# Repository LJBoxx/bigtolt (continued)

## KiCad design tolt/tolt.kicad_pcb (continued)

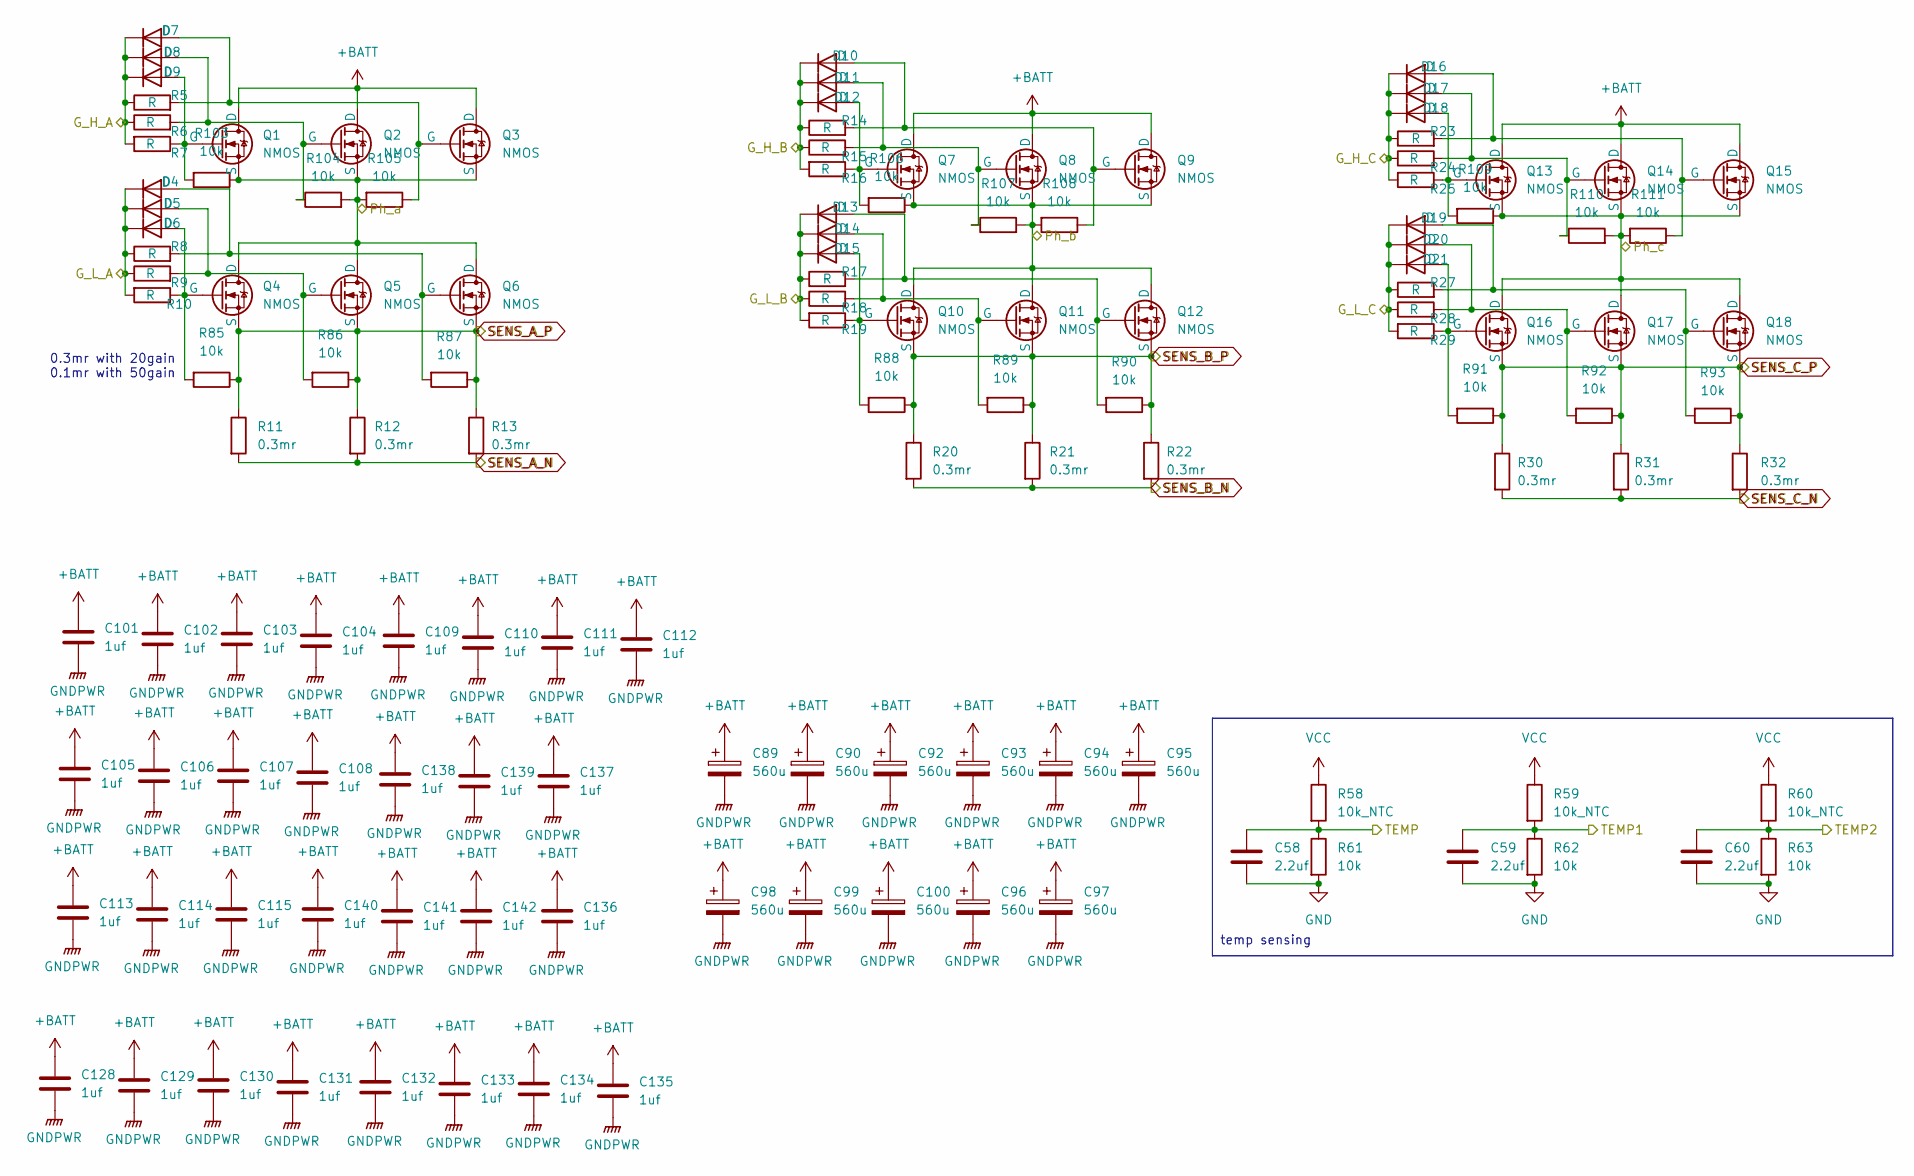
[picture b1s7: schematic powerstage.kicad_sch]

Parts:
C58, C59, C60: 2.2uf; C_0603_1608Metric
C89, C90, C92, C93, C94, C95, C96, C97, C98, C99, C100: 560u; CP_Radial_D16.0mm_P7.50mm
C101, C102, C103, C104, C105, C106, C107, C108, C109, C110, C111, C112, C113, C114, C115, C128, C129, C130, C131, C132, C133, C134, C135, C136, C137, C138, C139, C140, C141, C142: 1uf; C_2220_5750Metric_Pad1.97x5.40mm_HandSolder
D4, D5, D6, D7, D8, D9, D10, D11, D12, D13, D14, D15, D16, D17, D18, D19, D20, D21: D; D_SOD-123
Q1, Q2, Q3, Q4, Q5, Q6, Q7, Q8, Q9, Q10, Q11, Q12, Q13, Q14, Q15, Q16, Q17, Q18: NMOS; HDSOP-16-2
R5, R6, R7, R8, R9, R10, R14, R15, R16, R17, R18, R19, R23, R24, R25, R27, R28, R29: R; R_0805_2012Metric
R11, R12, R13, R20, R21, R22, R30, R31, R32: 0.3mr; R5930
R58, R59, R60: 10k_NTC; R_0603_1608Metric_Pad0.98x0.95mm_HandSolder
R61, R62, R63, R85, R86, R87, R88, R89, R90, R91, R92, R93, R103, R104, R105, R106, R107, R108, R109, R110, R111: 10k; R_0603_1608Metric

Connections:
+BATT: C89.1, C90.1, C92.1, C93.1, C94.1, C95.1, C96.1, C97.1, C98.1, C99.1, C100.1, C101.1, C102.1, C103.1, C104.1, C105.1, C106.1, C107.1, C108.1, C109.1, C110.1, C111.1, C112.1, C113.1, C114.1, C115.1, C128.1, C129.1, C130.1, C131.1, C132.1, C133.1, C134.1, C135.1, C136.1, C137.1, C138.1, C139.1, C140.1, C141.1, C142.1, Q1.1 (D), Q2.1 (D), Q3.1 (D), Q7.1 (D), Q8.1 (D), Q9.1 (D), Q13.1 (D), Q14.1 (D), Q15.1 (D); also elsewhere on the board
/INTER/G_H_A: D7.1 (K), D8.1 (K), D9.1 (K), R5.1, R6.1, R7.2; also elsewhere on the board
/INTER/G_H_B: D10.1 (K), D11.1 (K), D12.1 (K), R14.1, R15.1, R16.2; also elsewhere on the board
/INTER/G_H_C: D16.1 (K), D17.1 (K), D18.1 (K), R23.1, R24.1, R25.2; also elsewhere on the board
/INTER/G_L_A: D4.1 (K), D5.1 (K), D6.1 (K), R8.1, R9.1, R10.2; also elsewhere on the board
/INTER/G_L_B: D13.1 (K), D14.1 (K), D15.1 (K), R17.1, R18.1, R19.2; also elsewhere on the board
/INTER/G_L_C: D19.1 (K), D20.1 (K), D21.1 (K), R27.1, R28.1, R29.2; also elsewhere on the board
/INTER/Ph_a: Q1.3 (S), Q2.3 (S), Q3.3 (S), Q4.1 (D), Q5.1 (D), Q6.1 (D), R103.1, R104.2, R105.2; also elsewhere on the board
/INTER/Ph_b: Q7.3 (S), Q8.3 (S), Q9.3 (S), Q10.1 (D), Q11.1 (D), Q12.1 (D), R106.1, R107.2, R108.2; also elsewhere on the board
/INTER/Ph_c: Q13.3 (S), Q14.3 (S), Q15.3 (S), Q16.1 (D), Q17.1 (D), Q18.1 (D), R109.1, R110.2, R111.2; also elsewhere on the board
/logic/ADC_T1: C58.1, R58.2, R61.1; also elsewhere on the board
/logic/ADC_T2: C59.1, R59.2, R62.1; also elsewhere on the board
/logic/ADC_T3: C60.1, R60.2, R63.1; also elsewhere on the board
GND: C58.2, C59.2, C60.2, R61.2, R62.2, R63.2; also elsewhere on the board
GNDPWR: C89.2, C90.2, C92.2, C93.2, C94.2, C95.2, C96.2, C97.2, C98.2, C99.2, C100.2, C101.2, C102.2, C103.2, C104.2, C105.2, C106.2, C107.2, C108.2, C109.2, C110.2, C111.2, C112.2, C113.2, C114.2, C115.2, C128.2, C129.2, C130.2, C131.2, C132.2, C133.2, C134.2, C135.2, C136.2, C137.2, C138.2, C139.2, C140.2, C141.2, C142.2; also elsewhere on the board
unnamed: D4.2 (A), Q6.2 (G), R8.2, R87.2
unnamed: D5.2 (A), Q5.2 (G), R9.2, R86.2
unnamed: D6.2 (A), Q4.2 (G), R10.1, R85.2
unnamed: D7.2 (A), Q3.2 (G), R5.2, R105.1
unnamed: D8.2 (A), Q2.2 (G), R6.2, R104.1
unnamed: D9.2 (A), Q1.2 (G), R7.1, R103.2
unnamed: D10.2 (A), Q9.2 (G), R14.2, R108.1
unnamed: D11.2 (A), Q8.2 (G), R15.2, R107.1
unnamed: D12.2 (A), Q7.2 (G), R16.1, R106.2
unnamed: D13.2 (A), Q12.2 (G), R17.2, R90.2
unnamed: D14.2 (A), Q11.2 (G), R18.2, R89.2
unnamed: D15.2 (A), Q10.2 (G), R19.1, R88.2
unnamed: D16.2 (A), Q15.2 (G), R23.2, R111.1
unnamed: D17.2 (A), Q14.2 (G), R24.2, R110.1
unnamed: D18.2 (A), Q13.2 (G), R25.1, R109.2
unnamed: D19.2 (A), Q18.2 (G), R27.2, R93.2
unnamed: D20.2 (A), Q17.2 (G), R28.2, R92.2
unnamed: D21.2 (A), Q16.2 (G), R29.1, R91.2
SENS_A_N: R11.2, R12.2, R13.2; also elsewhere on the board
SENS_A_P: Q4.3 (S), Q5.3 (S), Q6.3 (S), R11.1, R12.1, R13.1, R85.1, R86.1, R87.1; also elsewhere on the board
SENS_B_N: R20.2, R21.2, R22.2; also elsewhere on the board
SENS_B_P: Q10.3 (S), Q11.3 (S), Q12.3 (S), R20.1, R21.1, R22.1, R88.1, R89.1, R90.1; also elsewhere on the board
SENS_C_N: R30.2, R31.2, R32.2; also elsewhere on the board
SENS_C_P: Q16.3 (S), Q17.3 (S), Q18.3 (S), R30.1, R31.1, R32.1, R91.1, R92.1, R93.1; also elsewhere on the board
VCC: R58.1, R59.1, R60.1; also elsewhere on the board

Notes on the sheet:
0.3mr with 20gain 0.1mr with 50gain
temp sensing

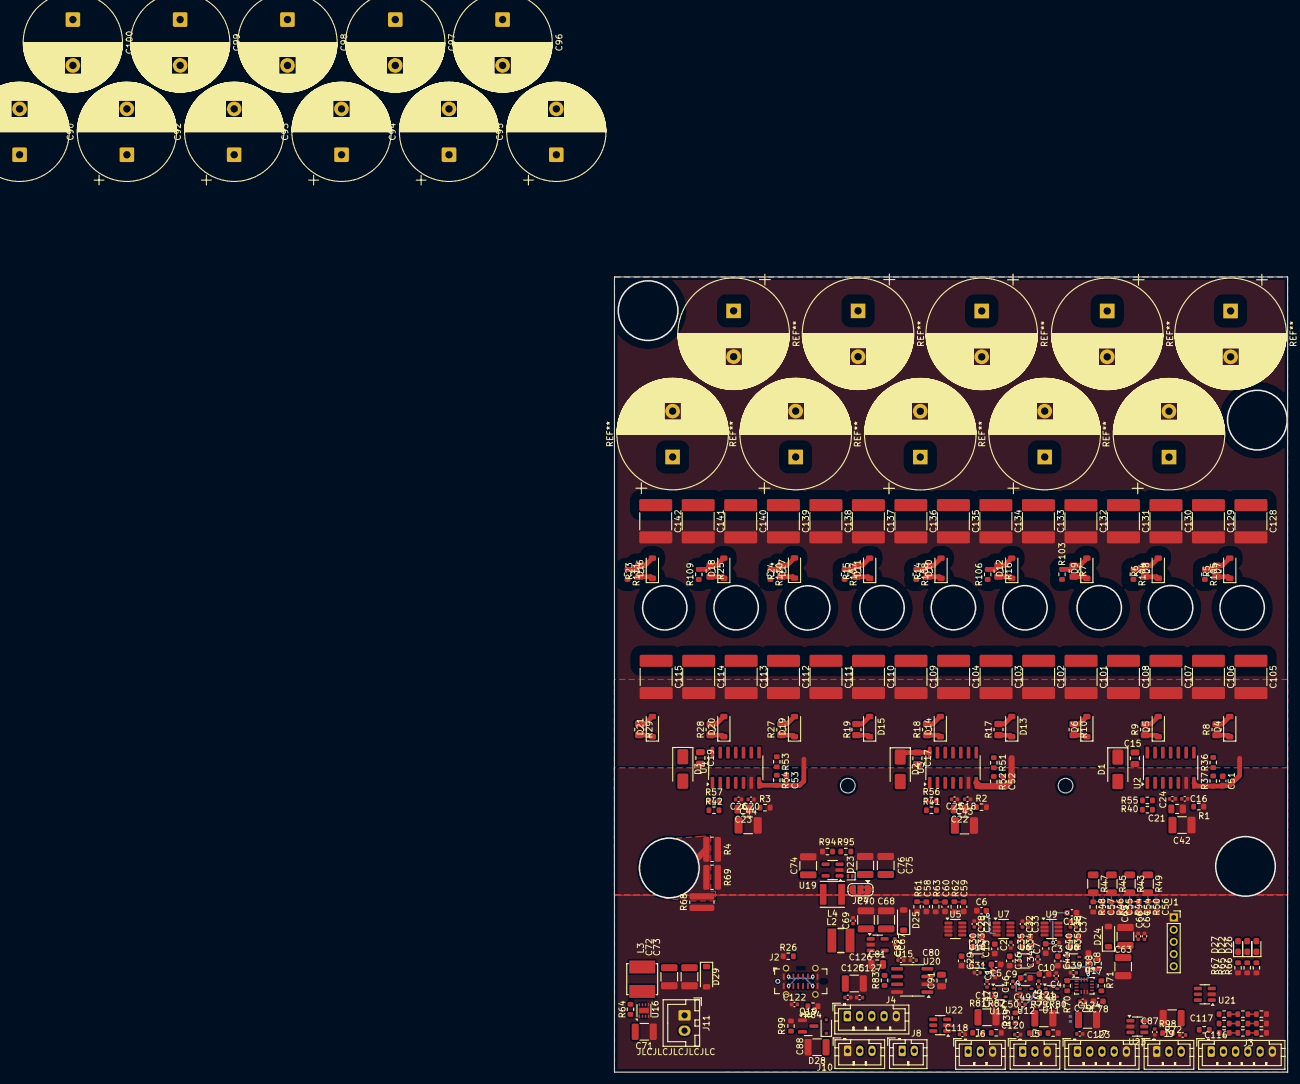
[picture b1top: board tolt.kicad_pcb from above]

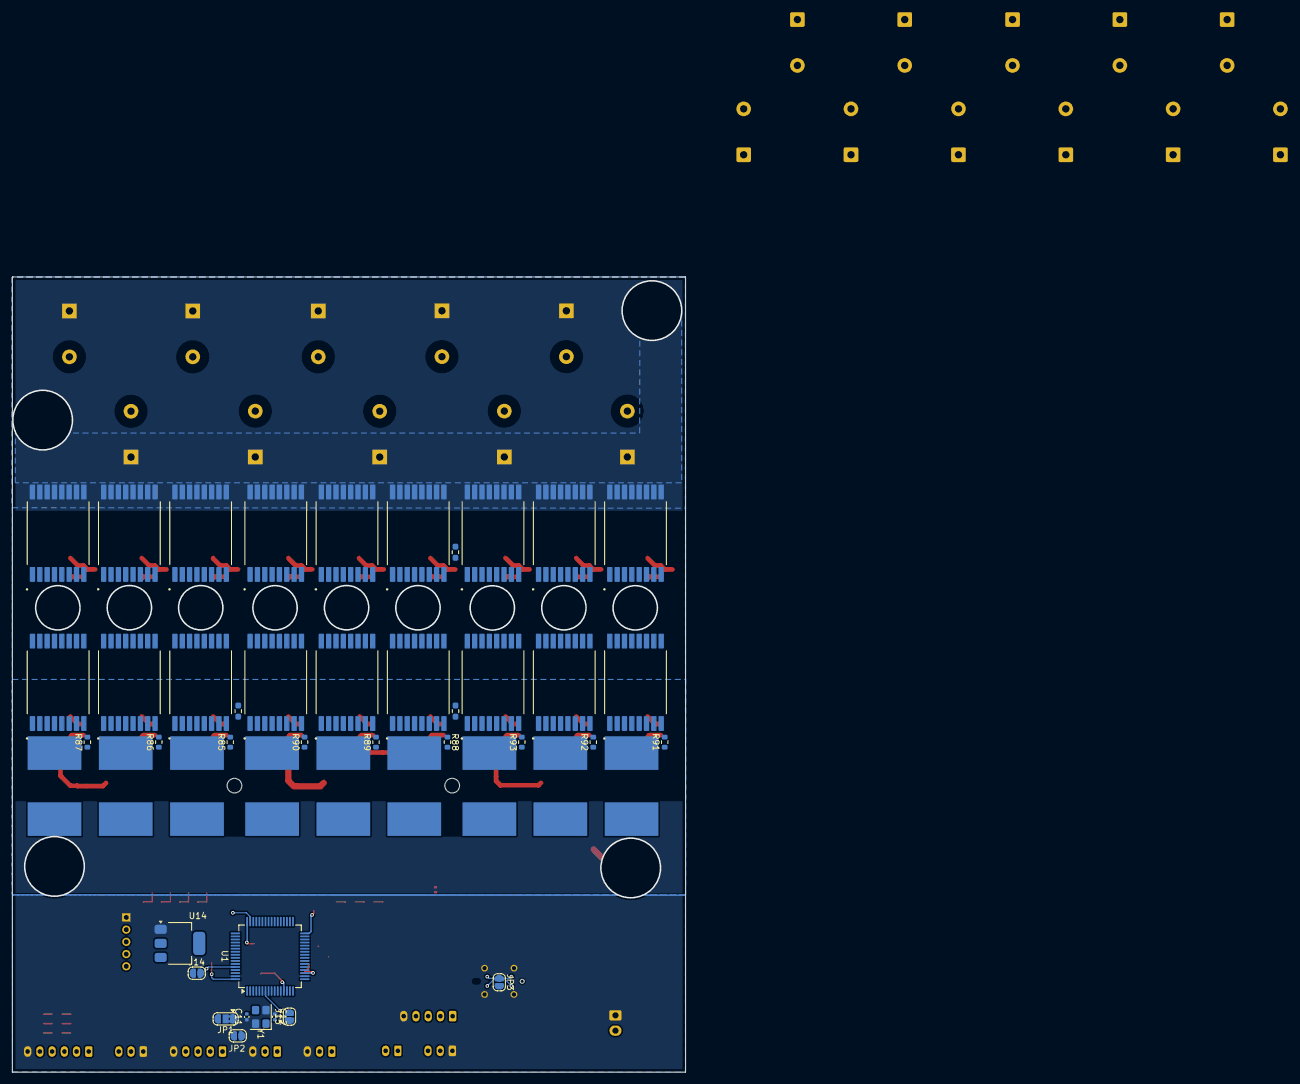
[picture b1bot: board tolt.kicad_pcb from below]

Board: 6 copper layers, 110.1 x 130.0 mm, 335 parts (49 on the bottom side), 130 nets.

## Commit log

2025-07-04 new file: tolt/desktop.ini new file: tolt/stm32.kicad_sch new file: tolt/tolt.kicad_pcb new file: tolt/tolt.kicad_pro new file: tolt/tolt.kicad_sch
2025-07-04 deleted: tolt/desktop.ini
2025-07-04 new file: tolt/inter.kicad_sch modified: tolt/tolt.kicad_pro modified: tolt/tolt.kicad_sch
2025-07-05 link
2025-07-05 new file: tolt/sheet.kicad_wks modified: tolt/sheet.kicad_wks modified: tolt/tolt.kicad_pro modified: tolt/tolt.kicad_sch
2025-07-05 modified: tolt/sheet.kicad_wks modified: tolt/tolt.kicad_pro modified: tolt/tolt.kicad_sch
2025-07-05 modified: tolt/inter.kicad_sch modified: tolt/stm32.kicad_sch
2025-07-05 new file: tolt/powerstage.kicad_sch modified: tolt/stm32.kicad_sch modified: tolt/tolt.kicad_pro modified: tolt/tolt.kicad_sch
2025-07-05 modified: tolt/inter.kicad_sch modified: tolt/powerstage.kicad_sch
2025-07-06 i hate RC Filters
2025-07-06 modified: tolt/inter.kicad_sch modified: tolt/stm32.kicad_sch modified: tolt/tolt.kicad_sch
2025-07-06 modified: tolt/inter.kicad_sch modified: tolt/powerstage.kicad_sch modified: tolt/stm32.kicad_sch modified: tolt/tolt.kicad_sch
2025-07-07 Converters
2025-07-07 new file: ESP32-C3_SUPERMINI_SMD.step new file: tolt/Library.pretty/MODULE_ESP32-C3_SUPERMINI.kicad_mod new file: tolt/auxl.kicad_sch
2025-07-08 modified: tolt/converters.kicad_sch modified: tolt/inter.kicad_sch modified: tolt/stm32.kicad_sch modified: tolt/tolt.kicad_pcb modified: tolt/tolt.kicad_pro modified: tolt/tolt.kicad_sch
2025-07-08 modified: tolt/auxl.kicad_sch modified: tolt/converters.kicad_sch modified: tolt/powerstage.kicad_sch modified: tolt/stm32.kicad_sch modified: tolt/tolt.kicad_pcb modified: tolt/tolt.kicad_pro modifi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
2025-07-08 new file: SOP120P1500X235-17N.step new file: tolt/Library.pretty/HDSOP-16-2.kicad_mod new file: tolt/Library.pretty/R5930.kicad_mod new file: tolt/conn.kicad_sch
2025-07-09 Revert "Merge branch 'main' of https://github.com/LJBoxx/bigtolt"
    This reverts commit 648dc93627ac55c8b54fa74faadbb35a312ea564, reversing
    changes made to 972c1c2491e13322900779e00755fdd65e6f8c8a.
2025-07-09 Reapply "Merge branch 'main' of https://github.com/LJBoxx/bigtolt"
    This reverts commit 10d1035653869a11abcc4dc45a35a471baa73785.
2025-07-09 revert the mess
    i am stupid
2025-07-09 6 layer
2025-07-10 footprints
2025-07-11 new file: tolt/Library.pretty/IND-SMD_L3.9-W3.9-1.kicad_mod new file: tolt/Library.pretty/IND-SMD_L5.0-W5.0.kicad_mod modified: tolt/auxl.kicad_sch modified: tolt/conn.kicad_sch modified: tolt/conver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
2025-07-11 modified: tolt/converters.kicad_sch modified: tolt/inter.kicad_sch modified: tolt/tolt.kicad_sch
2025-07-11 new file: tolt/Library.pretty/PQDE6W.kicad_mod modified: tolt/auxl.kicad_sch modified: tolt/conn.kicad_sch modified: tolt/converters.kicad_sch modified: tolt/powerstage.kicad_sch modified: tolt/tolt.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
2025-07-12 modified: tolt/conn.kicad_sch modified: tolt/converters.kicad_sch modified: tolt/inter.kicad_sch modified: tolt/powerstage.kicad_sch modified: tolt/stm32.kicad_sch modified: tolt/tolt.kicad_pcb modif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
2025-07-13 some
2025-07-13 modified: tolt/conn.kicad_sch modified: tolt/powerstage.kicad_sch modified: tolt/stm32.kicad_sch modified: tolt/tolt.kicad_pcb modified: tolt/tolt.kicad_pro modified: tolt/tolt.kicad_sch
2025-07-14 Update PCB component placements and replace jumper
    Moved several SMD components to new coordinates for layout optimization. Removed J14 (BOOT0 solder jumper) and added JP4 (3-pad solder jumper) for converter section. Updated silkscreen and fab UUIDs 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
2025-07-14 modified: tolt/conn.kicad_sch modified: tolt/tolt.kicad_pcb modified: tolt/tolt.kicad_pro
2025-07-17 updated routing
2025-07-17 modified: tolt/stm32.kicad_sch modified: tolt/tolt.kicad_pcb modified: tolt/tolt.kicad_pro modified: tolt/tolt.kicad_sch
2025-07-18 schem change
2025-07-18 modified: tolt/tolt.kicad_pcb
2025-07-22 move comp
2025-07-31 converter edit
    2x ltc7137
2025-07-31 upsies i forgot something
2025-07-31 more changes
2025-08-01 more files :3
2025-08-03 uhh seems like near finish
2025-08-04 FINAL?
2025-08-08 modified: tolt/converters.kicad_sch modified: tolt/tolt.kicad_pcb
2025-08-09 Add files via upload
    License added :D
2025-08-09 Add files via upload
    license
2025-08-11 modified: tolt/auxl.kicad_sch modified: tolt/converters.kicad_sch modified: tolt/tolt.kicad_pcb
2025-08-12 FINAL
2025-08-13 aaaa
2025-08-14 ibom
2025-08-25 yaaaaaaa
2025-09-15 fixes
    to be reviewed furthermore
2025-09-24 some fixed and edit
    tbd : phase voltage sensing and adct1 wiring and add on/off switch
2025-09-25 added conn for aux 12v
    more tbd : add test points
2025-09-26 idk just pushed for github profile lol
2025-09-28 reorg and cleaning
2025-10-04 some drc checks
2025-10-19 test
2025-10-30 sch cleanup
    cleaned fet sheet and added ferrite bead
    Fixed some ground issues
2025-11-02 mmmmmmmmmmmmmmmmmmmmmmmmmmmmmmmmmmmmmmmmmmmmm
    mmmmmmmmmmmmmmmmmmmmmmmmmmmmmmmmmmmmmmmmmmmmmmmmmmmmmmmmmmmmmmmmmmmmmmmmmmmmmmmmmmmmmmmmmmmmmmmmmmmmmmmmmmmmmmmmmmmmmmmmmmmmmmmmmmmmmmmmmmmmmmmmmmmmmmmmmmmmmmmmmmmmmmmmmmmmmmmmmmmmmmmmmmmmmmmmmmmmmmm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
2025-11-02 finished routing
    AAAAAAAAAAAAAAAAaaAAAAAAAAAAAAAAAAaaAAAAAAAAAAAAAAAAaaAAAAAAAAAAAAAAAAaaAAAAAAAAAAAAAAAAaaAAAAAAAAAAAAAAAAaaAAAAAAAAAAAAAAAAaaAAAAAAAAAAAAAAAAaaAAAAAAAAAAAAAAAAaaAAAAAAAAAAAAAAAAaaAAAAAAAAAAAAAAAAaa
    PLZ WORK PLZ WORK PLZ WORK PLZ WORK PLZ WORK PLZ WORK PLZ WORK PLZ WORK PLZ WORK PLZ WORK PLZ WORK PLZ WORK PLZ WORK PLZ WORK PLZ WORK PLZ WORK PLZ WORK PLZ WORK PLZ WORK PLZ WORK PLZ WORK PLZ WORK P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
2025-11-02 Update tolt.kicad_pcb
    oops forgot to save file
2025-11-03 some edits
    mostly pcb
2025-11-03 moar
    okay drc ran
2025-11-03 usb conn
    changed usb conn to flat
2025-11-17 big update
    fixed decoupling correctly
    more gnd plane work and routing finished
2025-11-18 extra buck added
    placed and routed
2025-11-21 12vdc
2025-12-02 few edit
2025-12-11 begenning of lcsc part assign
2025-12-13 more assign+12-5v change
    changed with TPS82130
    Since using esp32 will increase consumption by a lot
2025-12-15 hm
    weird huh it didnt fucking save
2025-12-21 Done
    hopefully finished ?
    needs sanity check and more checks
2025-12-22 fab
    finally.
2026-03-14 readme + cleanup
2026-03-14 oopsies
